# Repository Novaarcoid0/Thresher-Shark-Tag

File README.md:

# Thresher-Shark-Tag
This is a shark tag which will monitor the behaviour of the shark by using the heart rate and comparing it with the location (gps). It will also use a hydroelectric generator to get an infinite energy source. This tag will use a microphone to help scientists identify sounds underwater near the shark. This repository will include the CAD and the source code for the tag. If you have any questions, please email yrajpurkar11@gmail.com .

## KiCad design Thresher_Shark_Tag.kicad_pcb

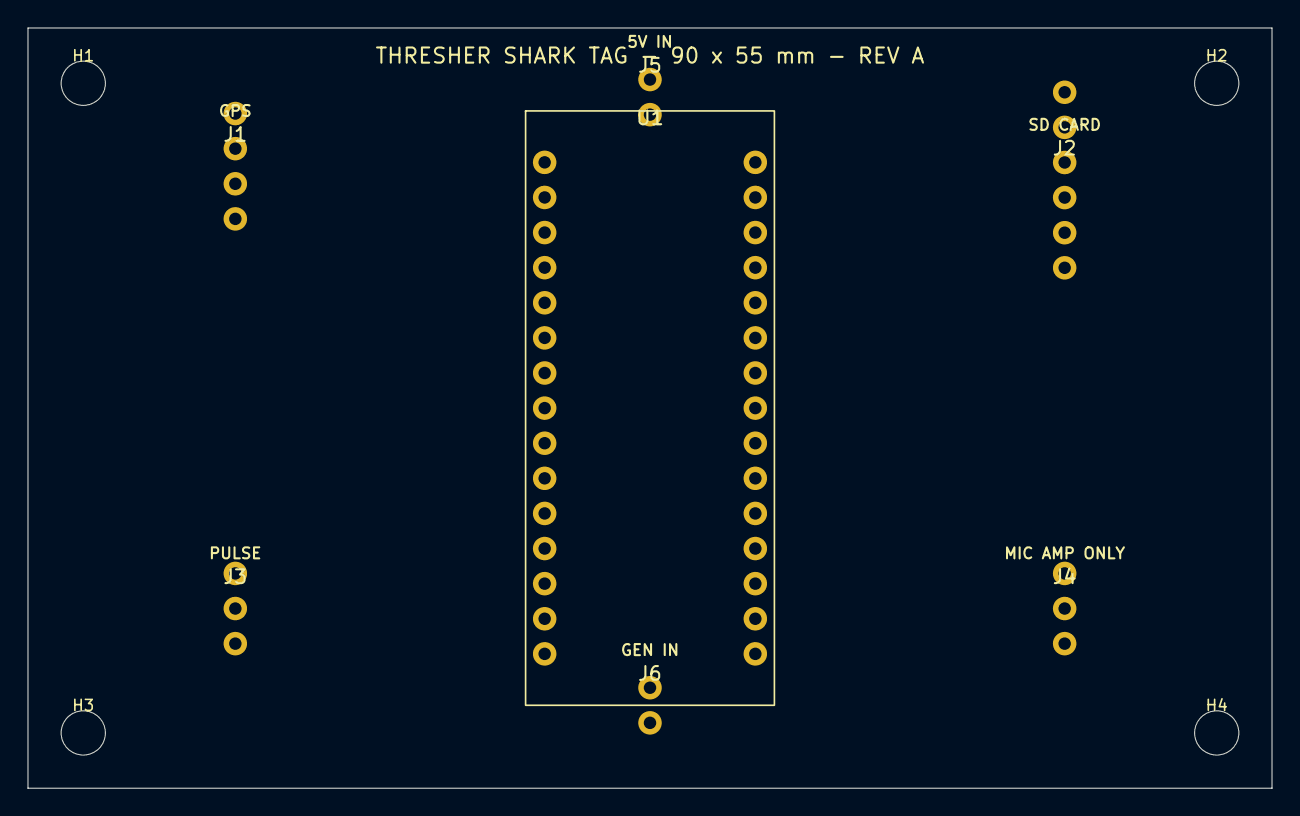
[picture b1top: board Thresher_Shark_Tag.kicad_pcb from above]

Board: 2 copper layers, 90.0 x 55.0 mm, 11 parts (0 on the bottom side), 2 nets, no tracks yet.

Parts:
H1, H2, H3, H4: M3 HOLE; MountingHole_3.2mm
J1: GPS NEO-6M (VCC,GND,TX,RX); Header_4
J2: MICROSD MODULE (VCC,GND,MISO,MOSI,SCK,CS); Header_6
J3: PULSESENSOR (VCC,GND,SIGNAL); Header_3
J4: MIC AMP OUTPUT (VCC,GND,OUT); Header_3
J5: REGULATED 5V INPUT; Header_2
J6: GENERATOR INPUT TO POWER CONDITIONER; Header_2
U1: ARDUINO NANO ATmega328P; Arduino_Nano_Classic_2x15

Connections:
5V: J1.1, J2.1, J3.1, J4.1, J5.1
GND: J1.2, J2.2, J3.2, J4.2, J5.2
